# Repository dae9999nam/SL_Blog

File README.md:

# Self-Learning Blog

###### This repository is to save all self-learning study records

### **_Content_**

#### Package: NumPy, Pandas, matplotlib, Sense-Hat, BeautifulSoup4, MQTT, GPIO
 
#### Technology: Jupyter notebook, LabVIEW, KiCad, Google Colab

#### CI: LabVIEW, graphical programming language tasks in rtf file format

#### IoT: Python programming with SenseHat, matplotlib, GPIO, MQTT tasks

#### ML/DL: Fundamental learning using PyTorch and Google Colab

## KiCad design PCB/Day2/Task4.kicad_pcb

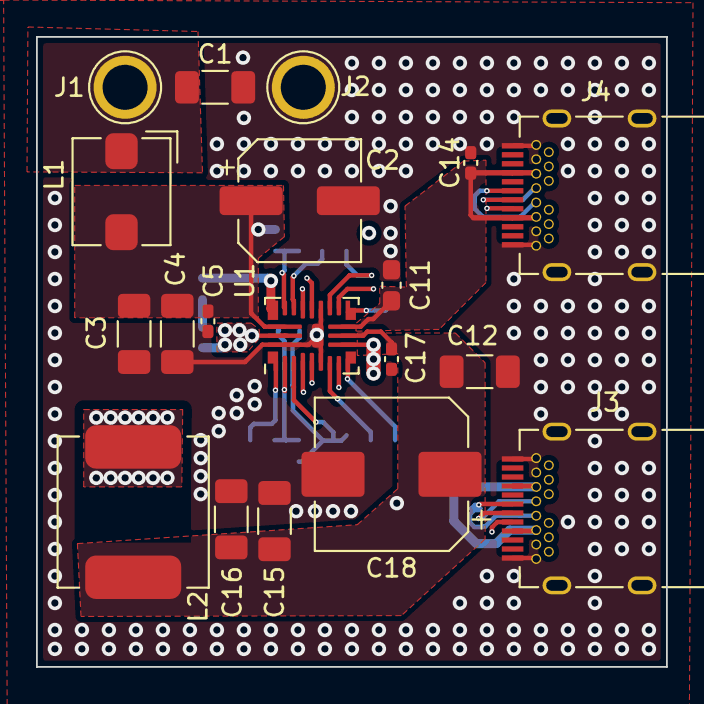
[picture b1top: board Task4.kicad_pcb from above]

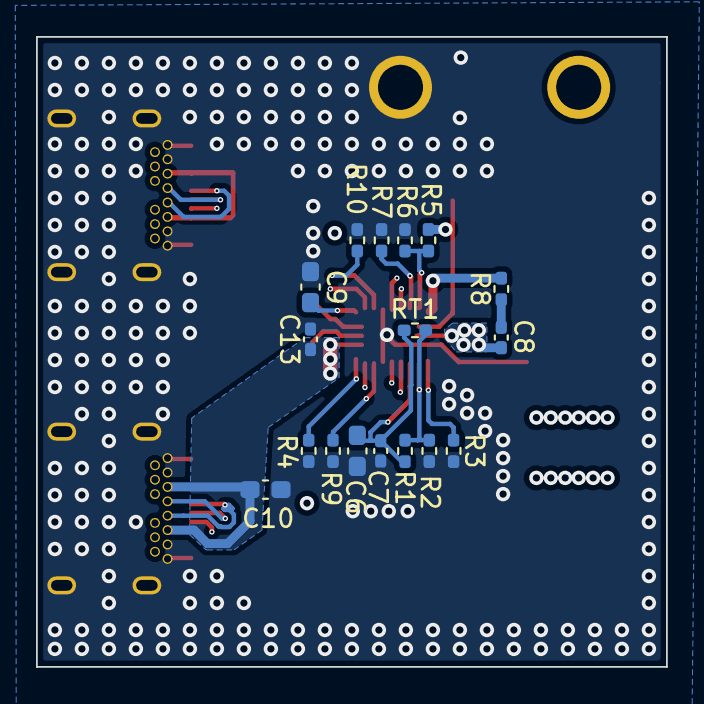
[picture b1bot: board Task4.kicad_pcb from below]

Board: 4 copper layers, 35.0 x 35.0 mm, 36 parts (17 on the bottom side), 23 nets.

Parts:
C1, C3, C4: 10U/50V; C_1206_3216Metric_Pad1.33x1.80mm_HandSolder
C2: 100U/50V; CP_Elec_6.3x5.8
C5, C8, C13, C14, C17: 0U1/50V; C_0402_1005Metric_Pad0.74x0.62mm_HandSolder
C6, C9: 2U2/10V; C_0603_1608Metric_Pad1.08x0.95mm_HandSolder
C7: 0U1/16V; C_0402_1005Metric_Pad0.74x0.62mm_HandSolder
C10, C11: 1U/16V; C_0603_1608Metric_Pad1.08x0.95mm_HandSolder
C12, C15, C16: 22U/10V; C_1206_3216Metric_Pad1.33x1.80mm_HandSolder
C18: 330U/10V; CP_Elec_8x10
J1, J2: 1502-2; Terminal_Keystone_1502-2
J3, J4: USB_C_Plug_632723300011
L1: L-Wurth-5030; L_Wurth_5030
L2: L-Panasonic-ETQP4M4R7KVK; L_Panasonic_M0840
R1: 39K2/1%; R_0402_1005Metric_Pad0.72x0.64mm_HandSolder
R2: 18K7/1%; R_0402_1005Metric_Pad0.72x0.64mm_HandSolder
R3, R4, R8: 0; R_0402_1005Metric_Pad0.72x0.64mm_HandSolder
R5, R6: 20K; R_0402_1005Metric_Pad0.72x0.64mm_HandSolder
R7: 49K9/1%; R_0402_1005Metric_Pad0.72x0.64mm_HandSolder
R9, R10: 5K1; R_0402_1005Metric_Pad0.72x0.64mm_HandSolder
RT1: 470K; R_0402_1005Metric_Pad0.72x0.64mm_HandSolder
U1: TPS25858QRPQRQ1; RPQ0025A

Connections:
+5V: C6.1, C7.1, C12.1, C15.1, C16.1, C17.1, C18.1, L2.2, R1.1, RT1.1, U1.3, U1.11
/PA_BUS: C10.1, C13.1, J3.A4, J3.A9, J3.B4, J3.B9, U1.10
/PA_CC1: J3.A5, R9.2, U1.7
/PA_CC2: J3.B5, U1.8
/PA_DM: J3.A7, J3.B7, U1.5
/PA_DP: J3.A6, J3.B6, U1.4
/PB_BUS: C11.1, C14.1, J4.A4, J4.A9, J4.B4, J4.B9, U1.12
/PB_CC1: J4.A5, R10.2, U1.15
/PB_CC2: J4.B5, U1.14
/PB_DM: J4.A7, J4.B7, U1.17
/PB_DP: J4.A6, J4.B6, U1.18
GND: C1.2, C2.2, C3.2, C4.2, C5.2, C6.2, C7.2, C9.1, C10.2, C11.2, C12.2, C13.2, C14.2, C15.2, C16.2, C17.2, C18.2, J2.1, J3.A1, J3.A12, J3.B1, J3.B12, J3.M1, J3.M2, J3.S1, J3.S2, J3.S3, J3.S4, J4.A1, J4.A12, J4.B1, J4.B12, J4.M1, J4.M2, J4.S1, J4.S2, J4.S3, J4.S4, R2.2, R3.2, R4.2, R6.2, R7.2, R9.1, R10.1, U1.6, U1.16, U1.24, U1.25
unnamed: C1.1, J1.1, L1.1
unnamed: C8.1, L2.1, U1.23
unnamed: C8.2, R8.1
unnamed: C9.2, U1.13
unnamed: R1.2, R2.1, RT1.2, U1.2
unnamed: R3.1, U1.1
unnamed: R4.1, U1.9
unnamed: R5.2, R6.1, U1.20
unnamed: R7.1, U1.19
unnamed: R8.2, U1.21
VCC: C2.1, C3.1, C4.1, C5.1, L1.2, R5.1, U1.22

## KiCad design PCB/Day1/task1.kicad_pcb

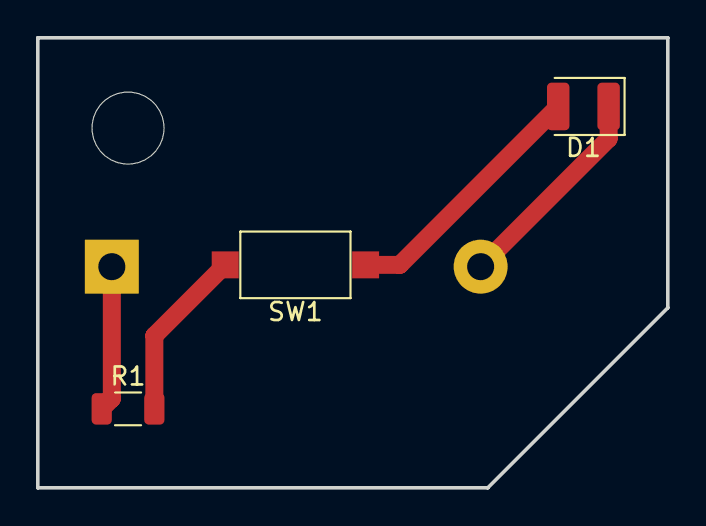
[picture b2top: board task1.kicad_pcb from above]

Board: 2 copper layers, 35.0 x 25.0 mm, 5 parts (1 on the bottom side), 4 nets.

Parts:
BT1: 103(CR2032); BatteryHolder_Keystone_103_1x20mm
D1: Red; LED_1210_3225Metric
H1: MountingHole; MountingHole_4mm
R1: 300R; R_1206_3216Metric
SW1: SW_Push; SW_SPST_CK_RS282G05A3

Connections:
unnamed: BT1.1, R1.1
unnamed: BT1.2, D1.1
unnamed: D1.2, SW1.1
unnamed: R1.2, SW1.2

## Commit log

2024-07-22 Second
2024-07-24 PCB Task Update
2024-07-24 PCB Task4 Update
2024-07-24 Data Analysis with Python update
2024-07-24 Data parsing using BS4 update
2024-07-24 SenseHat Task Update
2024-07-24 SenseHat Task Completed
2024-07-26 GPIO Task update
2024-07-26 ReadMe File update
2024-07-27 MQTT Task Update
2024-07-27 MQTT Task1 Update
2024-07-28 MQTT Task4 Update
2024-07-29 Colab을 통해 생성됨
2024-07-30 July30th update
2024-07-30 Jul 30th Update Colab
2024-07-30 Blog parsing code update
2024-07-31 Jul 31st Note Update
2024-07-31 Jul 31st Study update
2024-08-26 Aug 26 Note Updated
2024-08-26 Aug 26 new notebook updated
2024-08-26 Aug26 Notebook updated
2024-08-27 Aug 27 Notebook updated
2024-08-28 Aug 28 notebook updated
2024-08-28 Aug 28th Notebook chapter 3. trianing model updated
2024-08-28 Aug 29 Notebook updated
2024-09-17 Sep 17th Notebook Updated
2024-09-17 Sep 17th Notebook updated (Training Loop updated)
